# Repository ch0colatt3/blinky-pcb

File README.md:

# blinky-pcb

## Components

- x16+ Red LEDs
- x1 555 Timer IC
- x1 10 μF Capacitor
- x1 100k Variable Resistor
- x1 10k Resistor
- x1 330 ohm resistor
- x1 1 Push Button
- x1 9V Battery Holder Clip

## Description
This project is a hardware design of a 555 led chaser/blinky board. I made this double-layered pcb project following stasis’ & Athena’s Sleepover starter project. The software I used in the process is KiCad.

Process:
1. Use Kicad schematic editor to insert components /* idk if I used the right 55 timer IC */
2. Assign footprints to each component
3. Wire diagram 
4. Run electrical rules check(ERC) to fix any errors 
5. Export schematic to pcb editor
6. Import a dxf file of the image I want as my edge cut onto edge.cut layer(heel) /* this step took me hours, I downloaded Inkscape for this & tried to create a shape myself when the problem was that I forgot to put in on the correct layer, -I also had to adjust the shape of the heel to make sure if fitted the schematic(measurements, ratio) after I ran DRC :((  */
7. Arranged components inside heel shape
8. Route everything following highlighted blue lines on F.Cu or B.Cu(backside-if not enough space)
9. Run design rule check(DRC) to fix any errors (for me: unconnected wires, SILKSCREEN ISSUES) 
10. Use the text function and add design to board (I typed symbols & words) /*this step took me a few hours -rotating, making sure the text didn’t cause any errors or warnings */
11. Run DRC again 
12. Yippee!

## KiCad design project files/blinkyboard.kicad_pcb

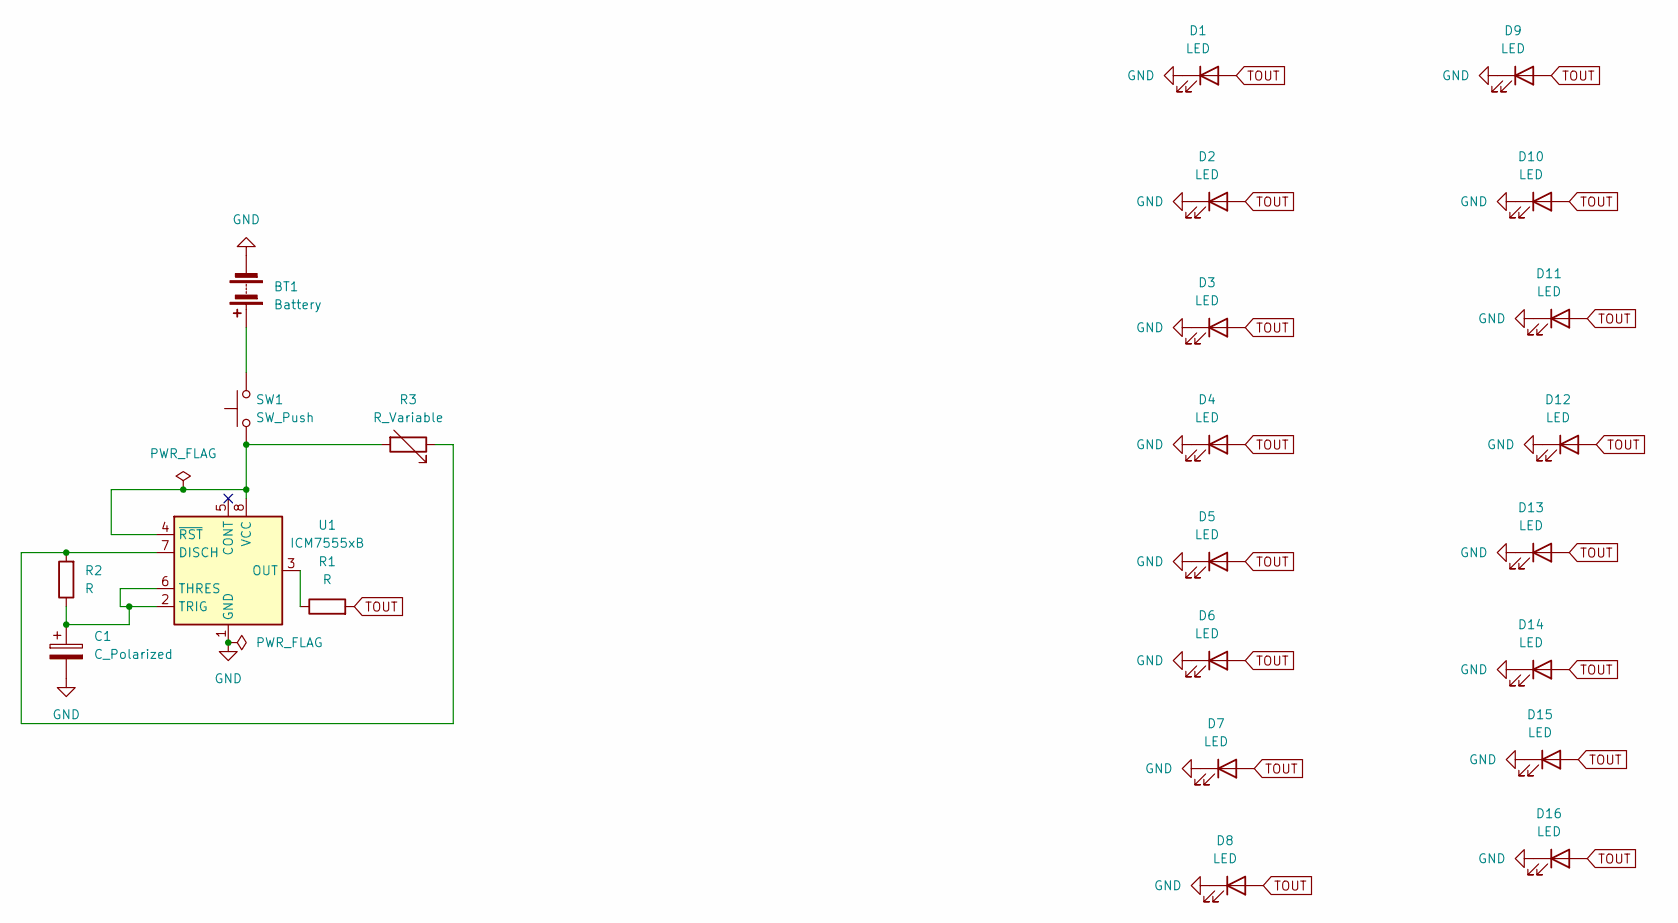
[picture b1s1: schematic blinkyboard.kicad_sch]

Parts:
BT1: Battery; SolderWire-0.1sqmm_1x02_P3.6mm_D0.4mm_OD1mm
C1: C_Polarized; CP_Radial_D5.0mm_P2.50mm
D1, D2, D3, D4, D5, D6, D7, D8, D9, D10, D11, D12, D13, D14, D15, D16: LED; LED_D5.0mm
R1, R2: R; R_Axial_DIN0207_L6.3mm_D2.5mm_P7.62mm_Horizontal
R3: R_Variable; Potentiometer_Bourns_3386P_Vertical
SW1: SW_Push; SW_PUSH_6mm
U1: ICM7555xB; SOIC-8_3.9x4.9mm_P1.27mm

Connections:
GND: BT1.2 (-), C1.2, D1.1 (K), D2.1 (K), D3.1 (K), D4.1 (K), D5.1 (K), D6.1 (K), D7.1 (K), D8.1 (K), D9.1 (K), D10.1 (K), D11.1 (K), D12.1 (K), D13.1 (K), D14.1 (K), D15.1 (K), D16.1 (K), U1.1 (GND)
unnamed: BT1.1 (+), SW1.2
unnamed: R2.2, R3.1, U1.7 (DISCH)
unnamed: R1.1, U1.3 (OUT)
unnamed: C1.1, R2.1, U1.2 (TRIG), U1.6 (THRES)
unnamed: R3.2, SW1.1, U1.4 (~RST), U1.8 (VCC)
TOUT: D1.2 (A), D2.2 (A), D3.2 (A), D4.2 (A), D5.2 (A), D6.2 (A), D7.2 (A), D8.2 (A), D9.2 (A), D10.2 (A), D11.2 (A), D12.2 (A), D13.2 (A), D14.2 (A), D15.2 (A), D16.2 (A), R1.2

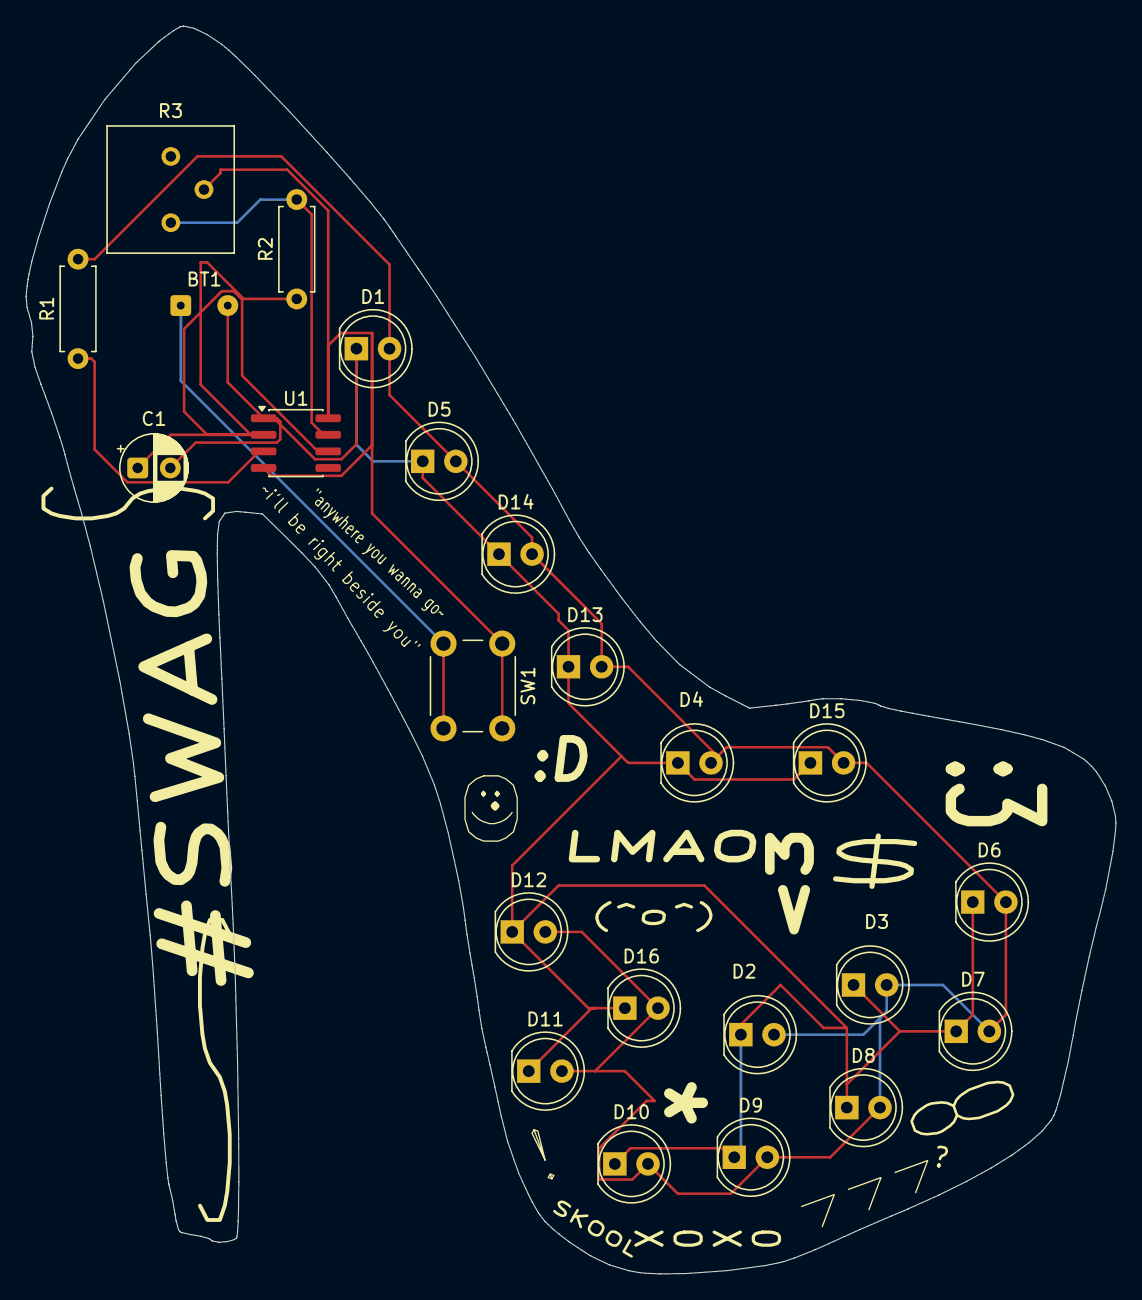
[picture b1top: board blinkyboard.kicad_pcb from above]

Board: 2 copper layers, 83.5 x 95.6 mm, 23 parts (0 on the bottom side), 7 nets.

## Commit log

2026-03-25 Create kicad project folder
2026-03-25 Rename kicad project folder to kicad project
2026-03-25 Create pcb
2026-03-26 Create kicad files
2026-03-26 Create s
2026-03-26 Rename s to blank
2026-03-29 Create *IMPORTANT - additional hours
2026-03-29 Rename pcb to blank
